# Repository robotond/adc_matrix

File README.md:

# adc_matrix
read 25 temperature sensors via 10 wires

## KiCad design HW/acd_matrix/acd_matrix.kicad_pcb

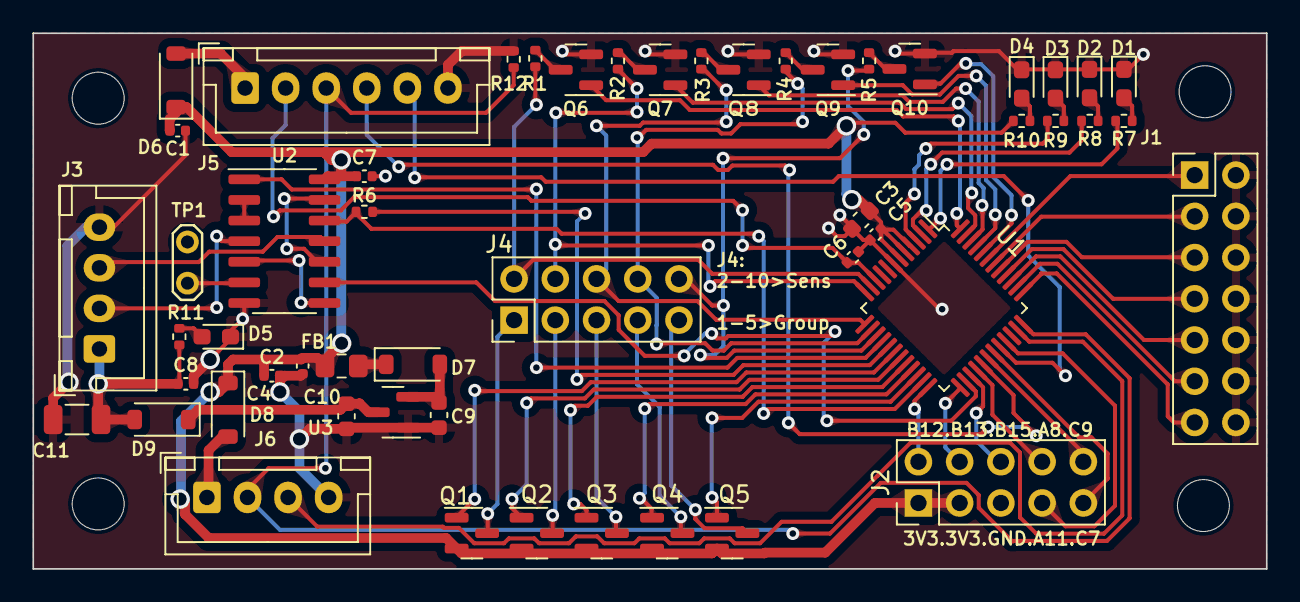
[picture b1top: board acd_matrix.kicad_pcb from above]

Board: 2 copper layers, 76.0 x 33.0 mm, 57 parts (0 on the bottom side), 70 nets.

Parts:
C1, C2, C4, C5, C6, C7, C8: 100nF; C_0402_1005Metric
C3, C9, C10: 1uF; C_0603_1608Metric
C11: 22uF; C_1206_3216Metric
D1: BLUE; LED_0603_1608Metric_Pad1.05x0.95mm_HandSolder
D2: GREEN; LED_0603_1608Metric_Pad1.05x0.95mm_HandSolder
D3: RED; LED_0603_1608Metric_Pad1.05x0.95mm_HandSolder
D4: WHITE; LED_0603_1608Metric_Pad1.05x0.95mm_HandSolder
D5: YELLOW; LED_0603_1608Metric_Pad1.05x0.95mm_HandSolder
D6, D7, D8, D9: B5819W; D_SOD-123
FB1: CBM201209U601T; L_0805_2012Metric_Pad1.15x1.40mm_HandSolder
J1: EXT1; PinHeader_2x07_P2.54mm_Vertical
J2: EXT2; PinHeader_2x05_P2.54mm_Vertical
J3: NODE; JST_XH_B4B-XH-A_1x04_P2.50mm_Vertical
J4: Probe; PinHeader_2x05_P2.54mm_Vertical
J5: BOOTLDR; JST_XH_B6B-XH-A_1x06_P2.50mm_Vertical
J6: SWD; JST_XH_B4B-XH-A_1x04_P2.50mm_Vertical
Q1, Q2, Q3, Q4, Q5: Si2301; SOT-23_GSD
Q6, Q7, Q8, Q9, Q10: Si2300A; SOT-23_GSD
R1, R2, R3, R4, R5, R6: 2k4; R_0402_1005Metric
R7, R8, R9, R10, R11, R12: 4k7; R_0402_1005Metric
REF1, REF2, REF3, REF4: MountingHole_3.2mm_M3
TP1: TestPoint; TestPoint_2Pads_Pitch2.54mm_Drill0.8mm
U1: STM32G070CBTx; LQFP-48_7x7mm_P0.5mm
U2: 74LV14; SOIC-14_3.9x8.7mm_P1.27mm
U3: HXY6206I-3V3; SOT-23

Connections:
+5V: C8.1, C11.1, D9.2 (A), J3.1, R11.1
/BLUE: R7.1, U1.1 (PC13)
/COL0: Q6.1 (G), U1.48 (PB9)
/COL1: Q7.1 (G), U1.47 (PB8)
/COL2: Q8.1 (G), U1.46 (PB7)
/COL3: Q9.1 (G), U1.45 (PB6)
/COL4: Q10.1 (G), U1.44 (PB5)
/GREEN: R8.1, U1.2 (PC14)
/N0: J4.1, Q1.3 (D)
/N1: J4.3, Q2.3 (D)
/N2: J4.5, Q3.3 (D)
/N3: J4.7, Q4.3 (D)
/N4: J4.9, Q5.3 (D)
/NRST: C6.1, J5.2, U1.10 (NRST)
/PA8: J2.8, U1.28 (PA8)
/PA11: J2.7, U1.33 (PA11/PA9)
/PA15: J1.13, U1.37 (PA15)
/PB3: J1.3, U1.42 (PB3)
/PB4: J1.1, U1.43 (PB4)
/PB12: J2.2, U1.24 (PB12)
/PB13: J2.4, U1.25 (PB13)
/PB15: J2.6, U1.27 (PB15)
/PC6: J2.10, U1.30 (PC6)
/PC7: J2.9, U1.31 (PC7)
/PD0: J1.11, U1.38 (PD0)
/PD1: J1.9, U1.39 (PD1)
/PD2: J1.7, U1.40 (PD2)
/PD3: J1.5, U1.41 (PD3)
/R0: Q1.1 (G), U1.18 (PA7)
/R1: Q2.1 (G), U1.19 (PB0)
/R2: Q3.1 (G), U1.20 (PB1)
/R3: Q4.1 (G), U1.21 (PB2)
/R4: Q5.1 (G), U1.22 (PB10)
/RED: R9.1, U1.3 (PC15)
/S0: J4.2, R1.1, U1.11 (PA0)
/S1: J4.4, R2.1, U1.12 (PA1)
/S2: J4.6, R3.1, U1.13 (PA2)
/S3: J4.8, R4.1, U1.14 (PA3)
/S4: J4.10, R5.1, U1.15 (PA4)
/START: R6.1, U1.17 (PA6)
/SWCLK_BT0: J5.3, J6.2, R12.1, U1.36 (PA14)
/SWDIO: J6.3, U1.35 (PA13)
/U1RX: J5.5, U1.32 (PA10/NC)
/U1TX: J5.4, U1.29 (PA9/NC)
/U3DE: U1.26 (PB14), U2.9
/U3RX: R6.2, U1.23 (PB11), U2.12
/U3TX: U1.16 (PA5), U2.1
GND: C1.2, C2.2, C3.2, C4.2, C5.2, C6.2, C7.2, C8.2, C9.2, C10.2, C11.2, D1.1 (K), D2.1 (K), D3.1 (K), D4.1 (K), D5.1 (K), J1.2, J1.4, J1.6, J1.8, J1.10, J1.12, J1.14, J2.5, J3.4, J5.6, J6.4, Q6.2 (S), Q7.2 (S), Q8.2 (S), Q9.2 (S), Q10.2 (S), R12.2, U1.7 (VSS), U2.7 (GND), U3.1 (VSS)
unnamed: C10.1, D9.1 (K), U3.3 (VIN)
unnamed: D1.2 (A), R7.2
unnamed: D2.2 (A), R8.2
unnamed: D3.2 (A), R9.2
unnamed: D4.2 (A), R10.2
unnamed: D5.2 (A), R11.2
unnamed: D6.2 (A), J5.1
unnamed: C9.1, D7.2 (A), U3.2 (VOUT)
unnamed: D7.1 (K), FB1.2
unnamed: D8.2 (A), J6.1
unnamed: J3.2, U2.4
unnamed: J3.3, U2.11
unnamed: Q6.3 (D), R1.2
unnamed: Q7.3 (D), R2.2
unnamed: Q8.3 (D), R3.2
unnamed: Q9.3 (D), R4.2
unnamed: Q10.3 (D), R5.2
unnamed: TP1.1, U2.6
unnamed: U2.2, U2.3
unnamed: U2.5, U2.8
unnamed: U2.10, U2.13
VDD: C1.1, C2.1, C3.1, C4.1, C5.1, C7.1, D6.1 (K), D8.1 (K), FB1.1, J2.1, J2.3, Q1.2 (S), Q2.2 (S), Q3.2 (S), Q4.2 (S), Q5.2 (S), R10.1, U1.4 (VBAT), U1.5 (VREF+), U1.6 (VDD), U2.14 (3.3V)

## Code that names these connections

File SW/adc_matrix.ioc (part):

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Mcu.Name=STM32G070CBTx
Mcu.Package=LQFP48
Mcu.UserName=STM32G070CBTx
PA0.GPIOParameters=GPIO_Label
PA0.GPIO_Label=S0
PA0.Mode=IN0
PA0.Signal=ADC1_IN0
PA1.GPIOParameters=GPIO_Label
PA1.GPIO_Label=S1
PA1.Mode=IN1
PA1.Signal=ADC1_IN1
PA10.Mode=Asynchronous
PA10.Signal=USART1_RX
PA11\ [PA9].GPIOParameters=GPIO_Label
PA11\ [PA9].GPIO_Label=PA11
PA11\ [PA9].Signal=GPIO_Output
PA12\ [PA10].GPIOParameters=GPIO_Label
PA12\ [PA10].GPIO_Label=PA12
PA12\ [PA10].Signal=GPIO_Output
PA13.GPIOParameters=GPIO_Label
PA13.GPIO_Label=SWDIO
PA13.Mode=Serial_Wire
PA13.Signal=SYS_SWDIO
PA14-BOOT0.GPIOParameters=GPIO_Label
PA14-BOOT0.GPIO_Label=SWCLK_BT0
PA14-BOOT0.Mode=Serial_Wire
PA14-BOOT0.Signal=SYS_SWCLK
PA15.GPIOParameters=GPIO_Label
PA15.GPIO_Label=PA15
PA15.Signal=GPIO_Output
PA2.GPIOParameters=GPIO_Label
PA2.GPIO_Label=S2
PA2.Mode=IN2
PA2.Signal=ADC1_IN2
PA3.GPIOParameters=GPIO_Label
PA3.GPIO_Label=S3
PA3.Mode=IN3
PA3.Signal=ADC1_IN3
PA4.GPIOParameters=GPIO_Label
PA4.GPIO_Label=S4
PA4.Mode=IN4
PA4.Signal=ADC1_IN4
PA5.GPIOParameters=GPIO_Label
PA5.GPIO_Label=U3TX
PA5.Mode=Asynchronous
PA5.Signal=USART3_TX
PA6.GPIOParameters=GPIO_Label
PA6.GPIO_Label=START
PA6.Signal=GPIO_Input
PA7.GPIOParameters=GPIO_Label
PA7.GPIO_Label=R0
PA7.Signal=GPIO_Output
PA8.GPIOParameters=GPIO_Label
PA8.GPIO_Label=PA8
PA8.Signal=GPIO_Output
PA9.Mode=Asynchronous
PA9.Signal=USART1_TX
PB0.GPIOParameters=GPIO_Label
PB0.GPIO_Label=R1
PB0.Signal=GPIO_Output
PB1.GPIOParameters=GPIO_Label
PB1.GPIO_Label=R2
PB1.Signal=GPIO_Output
PB10.GPIOParameters=GPIO_Label
PB10.GPIO_Label=R4
PB10.Signal=GPIO_Output
PB11.GPIOParameters=GPIO_Label
PB11.GPIO_Label=U3RX
PB11.Mode=Asynchronous
PB11.Signal=USART3_RX
PB12.GPIOParameters=GPIO_Label
PB12.GPIO_Label=PB12
PB12.Signal=GPIO_Output
PB13.GPIOParameters=GPIO_Label
PB13.GPIO_Label=PB13
PB13.Signal=GPIO_Output
PB14.GPIOParameters=GPIO_Label
PB14.GPIO_Label=U3DE
PB14.Mode=Hardware Flow Control (RS485)
PB14.Signal=USART3_DE
PB15.GPIOParameters=GPIO_Label
PB15.GPIO_Label=PB15
PB15.Signal=GPIO_Output
PB2.GPIOParameters=GPIO_Label
PB2.GPIO_Label=R3
PB2.Signal=GPIO_Output
PB3.GPIOParameters=GPIO_Label
PB3.GPIO_Label=PB3
PB3.Signal=GPIO_Output
PB4.GPIOParameters=GPIO_Label
PB4.GPIO_Label=PB4
PB4.Signal=GPIO_Output
PB5.GPIOParameters=GPIO_Label
PB5.GPIO_Label=COL4
PB5.Signal=GPIO_Output
PB6.GPIOParameters=GPIO_Label
PB6.GPIO_Label=COL3
PB6.Signal=GPIO_Output
PB7.GPIOParameters=GPIO_Label
PB7.GPIO_Label=COL2
PB7.Signal=GPIO_Output
PB8.GPIOParameters=GPIO_Label
PB8.GPIO_Label=COL1
PB8.Signal=GPIO_Output
PB9.GPIOParameters=GPIO_Label
PB9.GPIO_Label=COL0
PB9.Signal=GPIO_Output
PC13.GPIOParameters=GPIO_Label
PC13.GPIO_Label=BLUE
PC13.Signal=GPIO_Output
PC14-OSC32_IN\ (PC14).GPIOParameters=GPIO_Label
PC14-OSC32_IN\ (PC14).GPIO_Label=GREEN
PC14-OSC32_IN\ (PC14).Signal=GPIO_Output
PC15-OSC32_OUT\ (PC15).GPIOParameters=GPIO_Label
PC15-OSC32_OUT\ (PC15).GPIO_Label=RED
PC15-OSC32_OUT\ (PC15).Signal=GPIO_Output
PC6.GPIOParameters=GPIO_Label
PC6.GPIO_Label=PC7
PC6.Signal=GPIO_Output
PC7.GPIOParameters=GPIO_Label
PC7.GPIO_Label=PC7
PC7.Signal=GPIO_Output
PD0.GPIOParameters=GPIO_Label
PD0.GPIO_Label=PD0
PD0.Signal=GPIO_Output
PD1.GPIOParameters=GPIO_Label
PD1.GPIO_Label=PD1
PD1.Signal=GPIO_Output
PD2.GPIOParameters=GPIO_Label
PD2.GPIO_Label=PD2
PD2.Signal=GPIO_Output
PD3.GPIOParameters=GPIO_Label
PD3.GPIO_Label=PD3
PD3.Signal=GPIO_Output
RCC.HSE_VALUE=8000000
RCC.SYSCLKFreq_VALUE=64000000
RCC.SYSCLKSource=RCC_SYSCLKSOURCE_PLLCLK
board=custom

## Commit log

2023-06-16 Schematic added PCB layout added
2023-06-30 Added SW folder and STM32CUBEIDE project
2023-06-30 4 ADC channels with 16 sensors working
2023-07-17 nothing remarkable
2023-07-17 import cubeide project and created .gitignore
2023-07-17 implemented communication
2023-07-22 changes in .gitignore
2023-08-04 Calibration branch initial commit
2023-08-04 calibration data format from probe
2023-08-06 Protocol seem OK 16bit values 16 sensors
2023-08-06 tempcalc function added
2023-08-06 unnesessary directories removed (ADC411, adc_matrix2_calib)
2023-08-06 temperatures now follow real values with some correctable errors
2023-08-06 added calibration table
2023-08-06 deleted all build files
2023-08-06 change linker script path to relative in project settings
2023-08-11 nominal Rntc table calibration
2023-08-11 probe_cal. data added
2023-08-11 added usage of unique nominal NTC resistances + a prototype of measuring function with average calculation
2023-08-20 Last probe flashed -20-
2023-08-21 IOC file now adjusted to hardware
2023-08-22 defined LIE_TEMPERATURE to lie 0 as sensors data. Comment define to use probes in normal mode
2023-08-24 sensor dummy data is sensor number
